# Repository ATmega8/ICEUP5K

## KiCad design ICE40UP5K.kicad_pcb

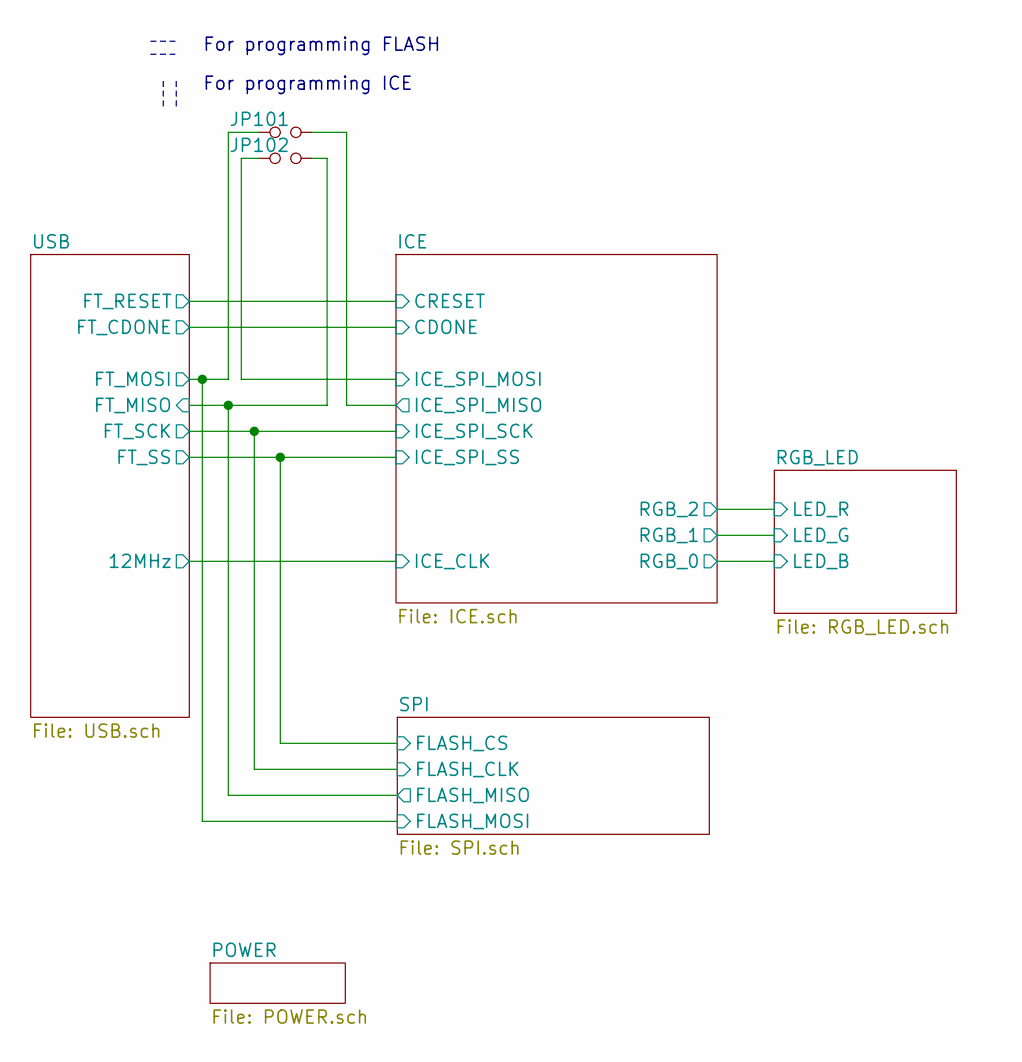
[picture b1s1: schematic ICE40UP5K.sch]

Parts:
JP101, JP102: Jumper_NO_Small; PinHeader_1x02_P2.54mm_Vertical

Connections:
/ICE/ICE_SPI_MISO: JP101.2; also elsewhere on the board
/ICE/ICE_SPI_MOSI: JP102.1; also elsewhere on the board
/SPI/FLASH_MISO: JP102.2; also elsewhere on the board
/SPI/FLASH_MOSI: JP101.1; also elsewhere on the board

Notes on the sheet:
For programming FLASH
For programming ICE

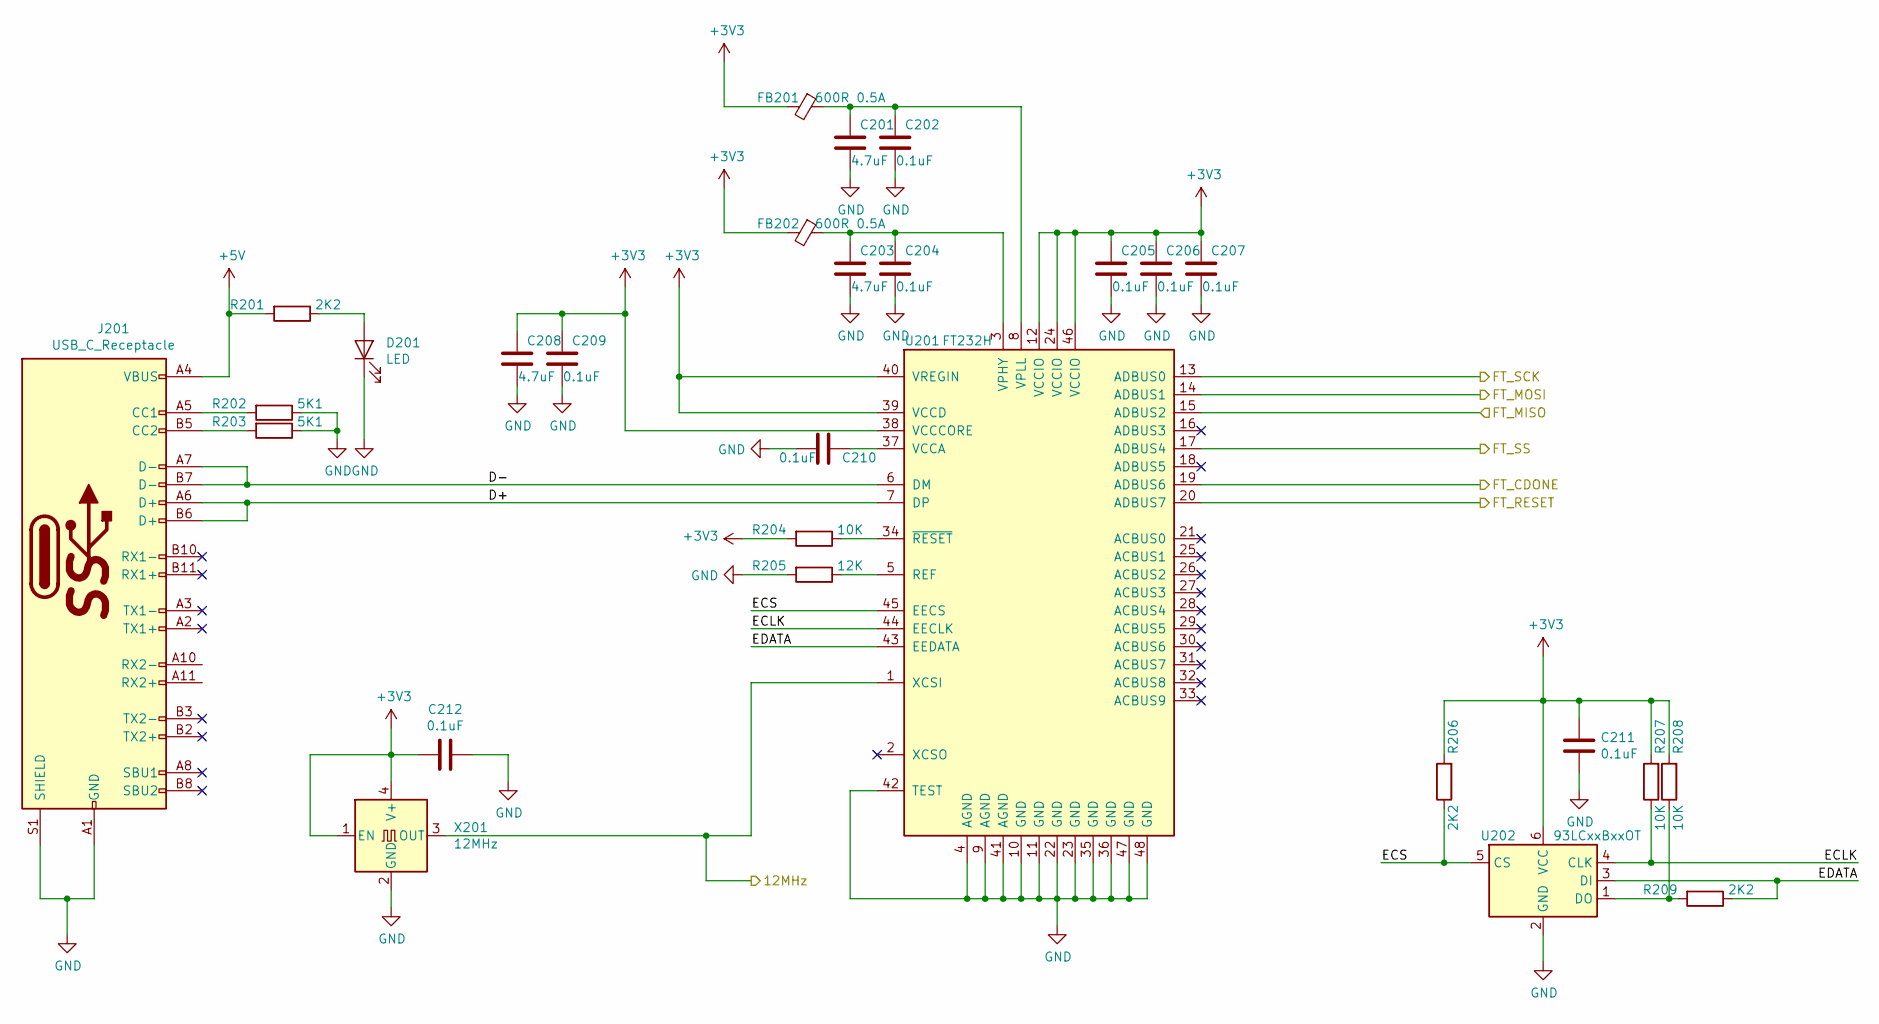
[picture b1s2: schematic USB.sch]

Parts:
C201, C203, C208: 4.7uF; C_0805_2012Metric
C202, C204, C205, C206, C207, C209, C210, C211, C212: 0.1uF; C_0603_1608Metric
D201: LED; LED_0603_1608Metric
FB201, FB202: 600R 0.5A; L_0805_2012Metric
J201: USB_C_Receptacle; USB_C_Receptacle_Palconn_UTC16-G
R201, R206, R209: 2K2; R_0603_1608Metric
R202, R203: 5K1; R_0603_1608Metric
R204, R207, R208: 10K; R_0603_1608Metric
R205: 12K; R_0603_1608Metric
U201: FT232H; LQFP-48_7x7mm_P0.5mm
U202: 93LCxxBxxOT; SOT-23-6
X201: 12MHz; Oscillator_SMD_EuroQuartz_XO32-4Pin_3.2x2.5mm_HandSoldering

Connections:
+3V3: C205.1, C206.1, C207.1, C208.1, C209.1, C211.1, C212.2, FB201.2, FB202.2, R204.2, R206.2, R207.2, R208.2, U201.12 (VCCIO), U201.24 (VCCIO), U201.38 (VCCCORE), U201.39 (VCCD), U201.40 (VREGIN), U201.46 (VCCIO), U202.6 (VCC), X201.1 (EN), X201.4 (V+); also elsewhere on the board
+5V: J201.A4 (VBUS), J201.A9 (VBUS), J201.B4 (VBUS), J201.B9 (VBUS), R201.2; also elsewhere on the board
/ICE/CDONE: U201.19 (ADBUS6); also elsewhere on the board
/ICE/CRESET: U201.20 (ADBUS7); also elsewhere on the board
/SPI/FLASH_CLK: U201.13 (ADBUS0); also elsewhere on the board
/SPI/FLASH_CS: U201.17 (ADBUS4); also elsewhere on the board
/SPI/FLASH_MISO: U201.15 (ADBUS2); also elsewhere on the board
/SPI/FLASH_MOSI: U201.14 (ADBUS1); also elsewhere on the board
/USB/12MHz: U201.1 (XCSI), X201.3 (OUT); also elsewhere on the board
/USB/D+: J201.A6 (D+), J201.B6 (D+), U201.7 (DP)
/USB/D-: J201.A7 (D-), J201.B7 (D-), U201.6 (DM)
/USB/ECLK: R207.1, U201.44 (EECLK), U202.4 (CLK)
/USB/ECS: R206.1, U201.45 (EECS), U202.5 (CS)
/USB/EDATA: R209.1, U201.43 (EEDATA), U202.3 (DI)
GND: C201.2, C202.2, C203.2, C204.2, C205.2, C206.2, C207.2, C208.2, C209.2, C210.2, C211.2, C212.1, D201.1 (K), J201.A1 (GND), J201.A12 (GND), J201.B1 (GND), J201.B12 (GND), J201.S1 (SHIELD), R202.1, R203.1, R205.2, U201.4 (AGND), U201.9 (AGND), U201.10 (GND), U201.11 (GND), U201.22 (GND), U201.23 (GND), U201.35 (GND), U201.36 (GND), U201.41 (AGND), U201.42 (TEST), U201.47 (GND), U201.48 (GND), U202.2 (GND), X201.2 (GND); also elsewhere on the board
unnamed: C201.1, C202.1, FB201.1, U201.8 (VPLL)
unnamed: C203.1, C204.1, FB202.1, U201.3 (VPHY)
unnamed: C210.1, U201.37 (VCCA)
unnamed: D201.2 (A), R201.1
unnamed: J201.A5 (CC1), R202.2
unnamed: J201.B5 (CC2), R203.2
unnamed: R204.1, U201.34 (~RESET)
unnamed: R205.1, U201.5 (REF)
unnamed: R208.1, R209.2, U202.1 (DO)

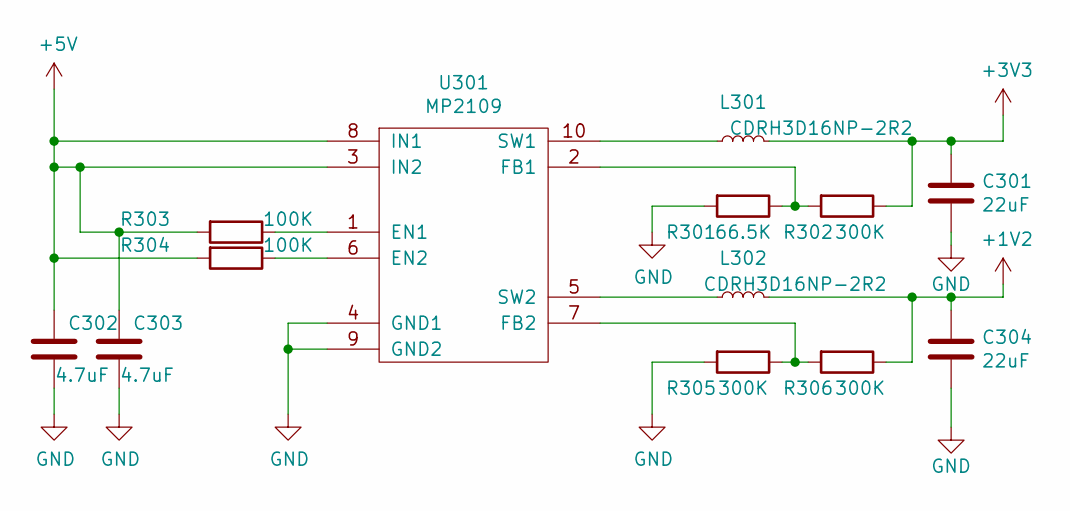
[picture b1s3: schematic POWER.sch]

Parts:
C301, C304: 22uF; C_0805_2012Metric
C302, C303: 4.7uF; C_0805_2012Metric
L301, L302: CDRH3D16NP-2R2; L_Wuerth_HCI-5040
R301: 66.5K; R_0603_1608Metric
R302, R305, R306: 300K; R_0603_1608Metric
R303, R304: 100K; R_0603_1608Metric
U301: MP2109; DFN-10-1EP_3x3mm_P0.5mm_EP1.65x2.38mm_ThermalVias

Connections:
+1V2: C304.1, L302.2, R306.1; also elsewhere on the board
+3V3: C301.1, L301.2, R302.1; also elsewhere on the board
+5V: C302.1, C303.1, R303.2, R304.2, U301.3 (IN2), U301.8 (IN1); also elsewhere on the board
GND: C301.2, C302.2, C303.2, C304.2, R301.2, R305.2, U301.4 (GND1), U301.9 (GND2); also elsewhere on the board
unnamed: L301.1, U301.10 (SW1)
unnamed: L302.1, U301.5 (SW2)
unnamed: R301.1, R302.2, U301.2 (FB1)
unnamed: R303.1, U301.1 (EN1)
unnamed: R304.1, U301.6 (EN2)
unnamed: R305.1, R306.2, U301.7 (FB2)

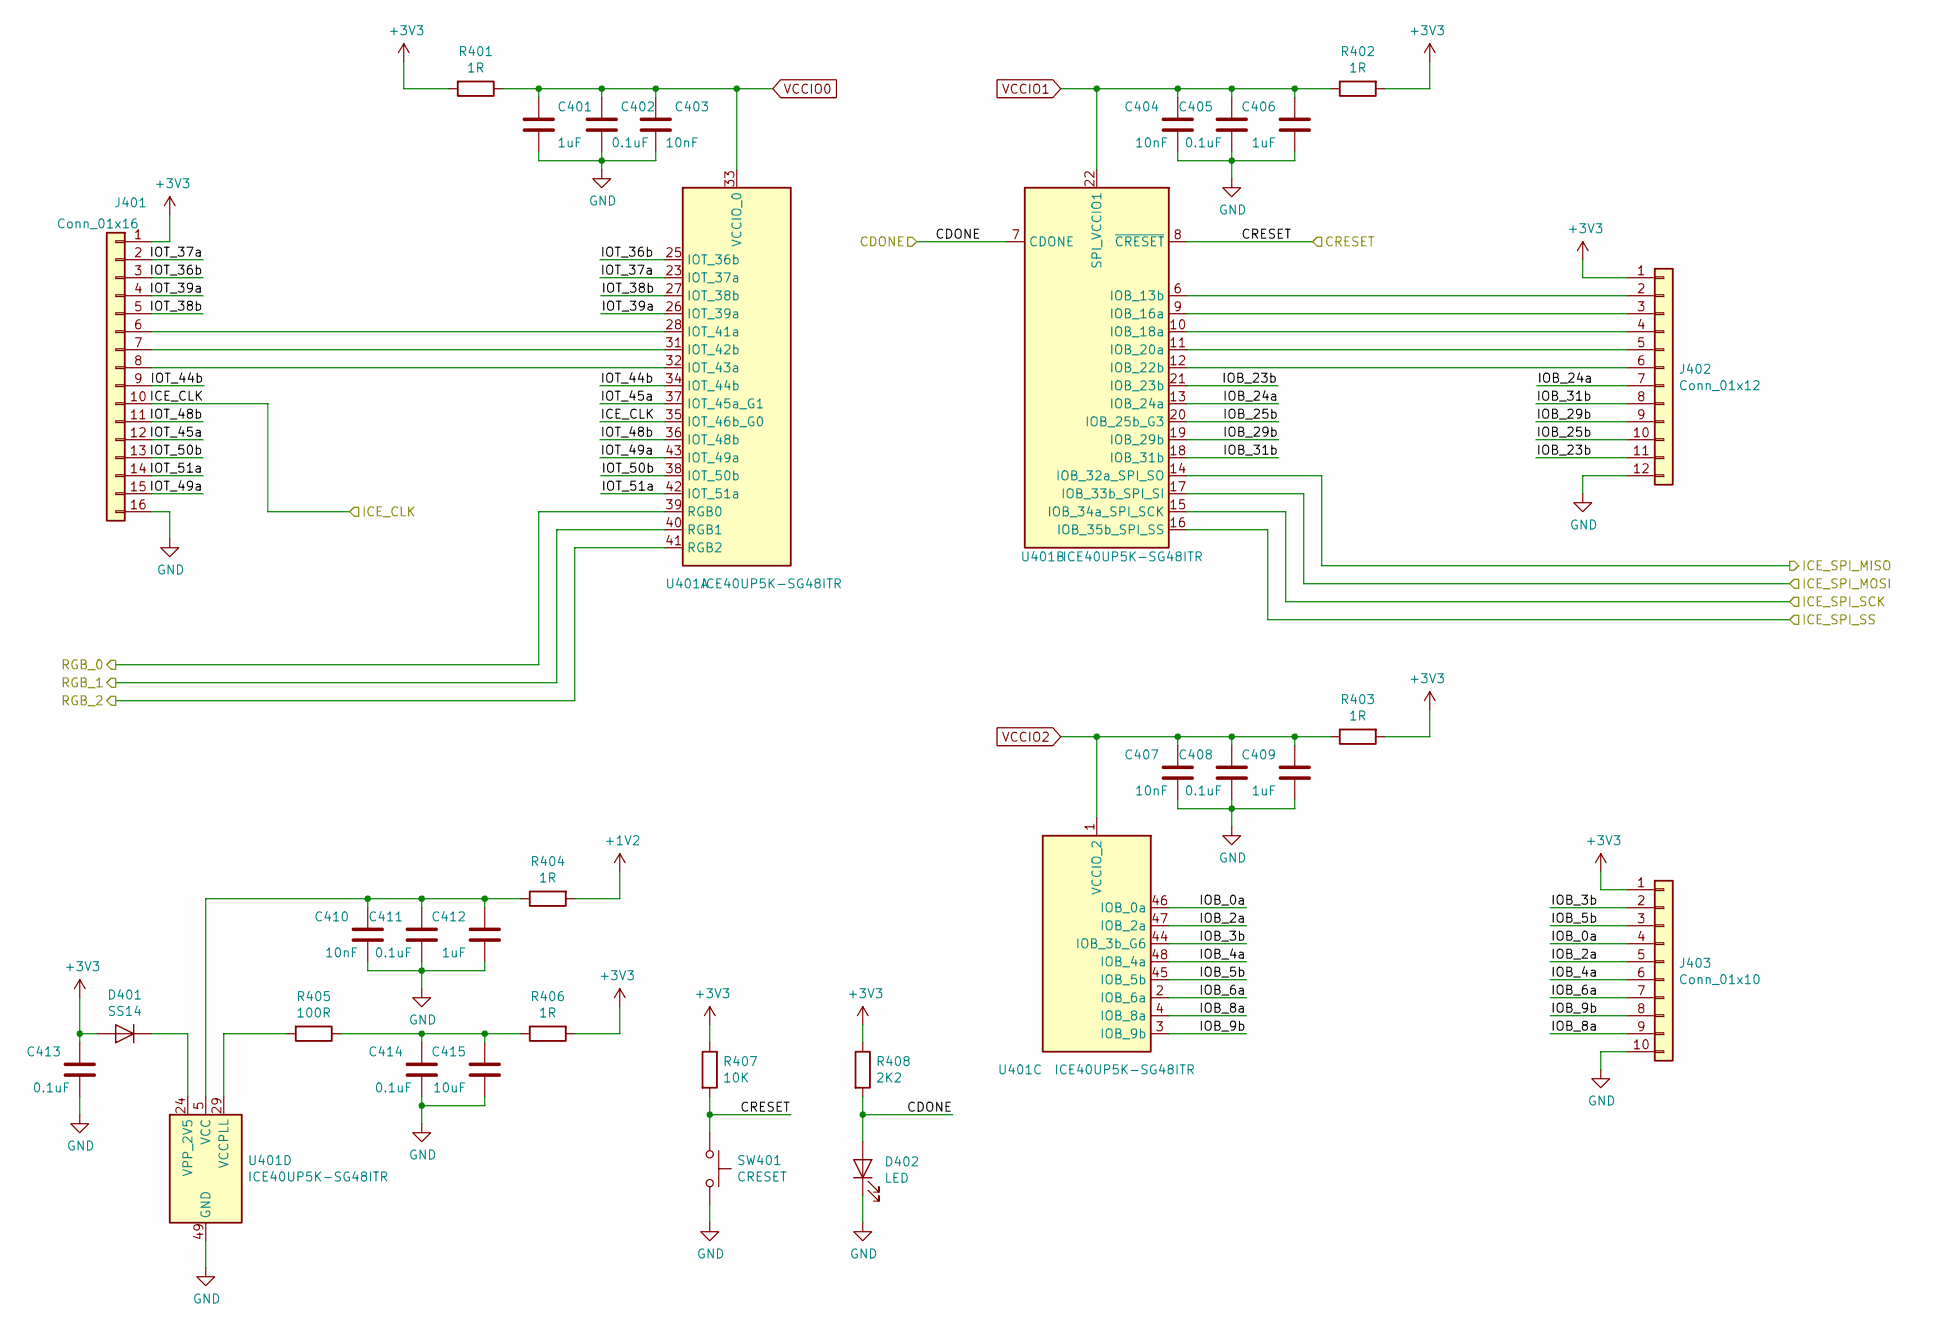
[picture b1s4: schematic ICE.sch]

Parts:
C401, C406, C409, C412: 1uF; C_0603_1608Metric
C402, C405, C408, C411, C413, C414: 0.1uF; C_0603_1608Metric
C403, C404, C407, C410: 10nF; C_0603_1608Metric
C415: 10uF; C_0805_2012Metric
D401: SS14; D_SOD-323_HandSoldering
D402: LED; LED_0603_1608Metric
J401: Conn_01x16; PinSocket_1x16_P2.54mm_Vertical
J402: Conn_01x12; PinSocket_1x12_P2.54mm_Vertical
J403: Conn_01x10; PinSocket_1x10_P2.54mm_Vertical
R401, R402, R403, R404, R406: 1R; R_0603_1608Metric
R405: 100R; R_0603_1608Metric
R407: 10K; R_0603_1608Metric
R408: 2K2; R_0603_1608Metric
SW401: CRESET; SW_SPST_TL3342
U401: ICE40UP5K-SG48ITR; QFN-48-1EP_7x7mm_P0.5mm_EP5.6x5.6mm

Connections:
+1V2: R404.2; also elsewhere on the board
+3V3: C413.1, D401.2 (A), J401.1, J402.1, J403.1, R401.2, R402.2, R403.2, R406.2, R407.1, R408.1; also elsewhere on the board
/ICE/CDONE: D402.2 (A), R408.2, U401.7 (CDONE); also elsewhere on the board
/ICE/CRESET: R407.2, SW401.1, U401.8 (~CRESET); also elsewhere on the board
/ICE/ICE_SPI_MISO: U401.14 (IOB_32a_SPI_SO); also elsewhere on the board
/ICE/ICE_SPI_MOSI: U401.17 (IOB_33b_SPI_SI); also elsewhere on the board
/ICE/IOB_0a: J403.4, U401.46 (IOB_0a)
/ICE/IOB_2a: J403.5, U401.47 (IOB_2a)
/ICE/IOB_3b: J403.2, U401.44 (IOB_3b_G6)
/ICE/IOB_4a: J403.6, U401.48 (IOB_4a)
/ICE/IOB_5b: J403.3, U401.45 (IOB_5b)
/ICE/IOB_6a: J403.7, U401.2 (IOB_6a)
/ICE/IOB_8a: J403.9, U401.4 (IOB_8a)
/ICE/IOB_9b: J403.8, U401.3 (IOB_9b)
/ICE/IOB_23b: J402.11, U401.21 (IOB_23b)
/ICE/IOB_24a: J402.7, U401.13 (IOB_24a)
/ICE/IOB_25b: J402.10, U401.20 (IOB_25b_G3)
/ICE/IOB_29b: J402.9, U401.19 (IOB_29b)
/ICE/IOB_31b: J402.8, U401.18 (IOB_31b)
/ICE/IOT_36b: J401.3, U401.25 (IOT_36b)
/ICE/IOT_37a: J401.2, U401.23 (IOT_37a)
/ICE/IOT_38b: J401.5, U401.27 (IOT_38b)
/ICE/IOT_39a: J401.4, U401.26 (IOT_39a)
/ICE/IOT_44b: J401.9, U401.34 (IOT_44b)
/ICE/IOT_45a: J401.12, U401.37 (IOT_45a_G1)
/ICE/IOT_48b: J401.11, U401.36 (IOT_48b)
/ICE/IOT_49a: J401.15, U401.43 (IOT_49a)
/ICE/IOT_50b: J401.13, U401.38 (IOT_50b)
/ICE/IOT_51a: J401.14, U401.42 (IOT_51a)
/RGB_LED/LED_B: U401.39 (RGB0); also elsewhere on the board
/RGB_LED/LED_G: U401.40 (RGB1); also elsewhere on the board
/RGB_LED/LED_R: U401.41 (RGB2); also elsewhere on the board
/SPI/FLASH_CLK: U401.15 (IOB_34a_SPI_SCK); also elsewhere on the board
/SPI/FLASH_CS: U401.16 (IOB_35b_SPI_SS); also elsewhere on the board
/USB/12MHz: J401.10, U401.35 (IOT_46b_G0); also elsewhere on the board
GND: C401.2, C402.2, C403.2, C404.2, C405.2, C406.2, C407.2, C408.2, C409.2, C410.2, C411.2, C412.2, C413.2, C414.2, C415.2, D402.1 (K), J401.16, J402.12, J403.10, SW401.2, U401.49 (GND); also elsewhere on the board
unnamed: C410.1, C411.1, C412.1, R404.1, U401.5 (VCC), U401.30 (VCC)
unnamed: C414.1, C415.1, R405.1, R406.1
unnamed: D401.1 (K), U401.24 (VPP_2V5)
unnamed: J401.6, U401.28 (IOT_41a)
unnamed: J401.7, U401.31 (IOT_42b)
unnamed: J401.8, U401.32 (IOT_43a)
unnamed: J402.2, U401.6 (IOB_13b)
unnamed: J402.3, U401.9 (IOB_16a)
unnamed: J402.4, U401.10 (IOB_18a)
unnamed: J402.5, U401.11 (IOB_20a)
unnamed: J402.6, U401.12 (IOB_22b)
unnamed: R405.2, U401.29 (VCCPLL)
VCCIO0: C401.1, C402.1, C403.1, R401.1, U401.33 (VCCIO_0)
VCCIO1: C404.1, C405.1, C406.1, R402.1, U401.22 (SPI_VCCIO1)
VCCIO2: C407.1, C408.1, C409.1, R403.1, U401.1 (VCCIO_2)

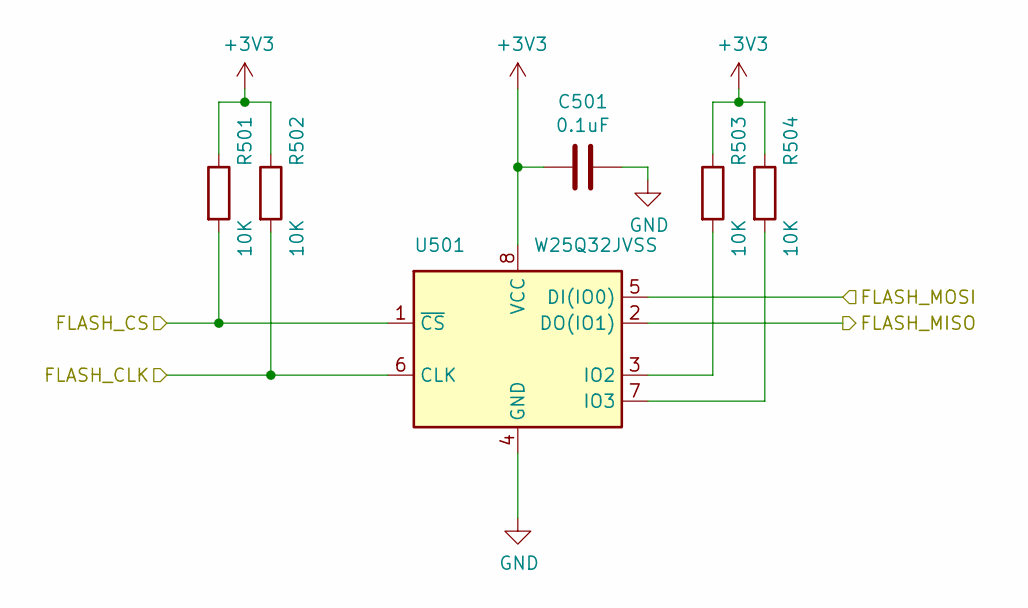
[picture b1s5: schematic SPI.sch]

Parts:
C501: 0.1uF; C_0603_1608Metric
R501, R502, R503, R504: 10K; R_0603_1608Metric
U501: W25Q32JVSS; SOIC-8_5.23x5.23mm_P1.27mm

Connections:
+3V3: C501.1, R501.1, R502.1, R503.1, R504.1, U501.8 (VCC); also elsewhere on the board
/SPI/FLASH_CLK: R502.2, U501.6 (CLK); also elsewhere on the board
/SPI/FLASH_CS: R501.2, U501.1 (~CS); also elsewhere on the board
/SPI/FLASH_MISO: U501.2 (DO(IO1)); also elsewhere on the board
/SPI/FLASH_MOSI: U501.5 (DI(IO0)); also elsewhere on the board
GND: C501.2, U501.4 (GND); also elsewhere on the board
unnamed: R503.2, U501.3 (IO2)
unnamed: R504.2, U501.7 (IO3)

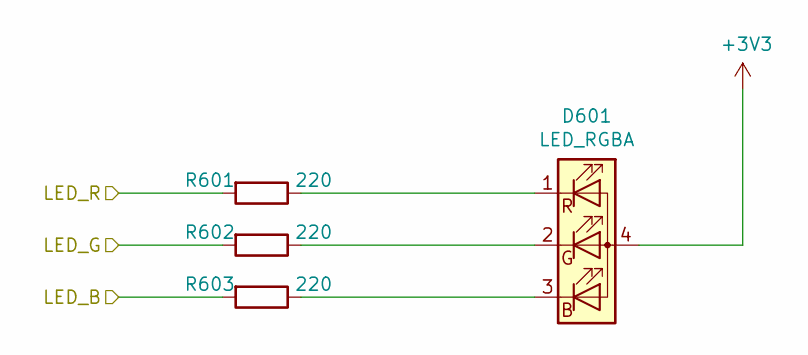
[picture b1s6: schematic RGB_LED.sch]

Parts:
D601: LED_RGBA; LED_Cree-PLCC4_2x2mm_CW
R601, R602, R603: 220; R_0603_1608Metric

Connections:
+3V3: D601.4 (A); also elsewhere on the board
/RGB_LED/LED_B: R603.2; also elsewhere on the board
/RGB_LED/LED_G: R602.2; also elsewhere on the board
/RGB_LED/LED_R: R601.2; also elsewhere on the board
unnamed: D601.1 (RK), R601.1
unnamed: D601.2 (GK), R602.1
unnamed: D601.3 (BK), R603.1

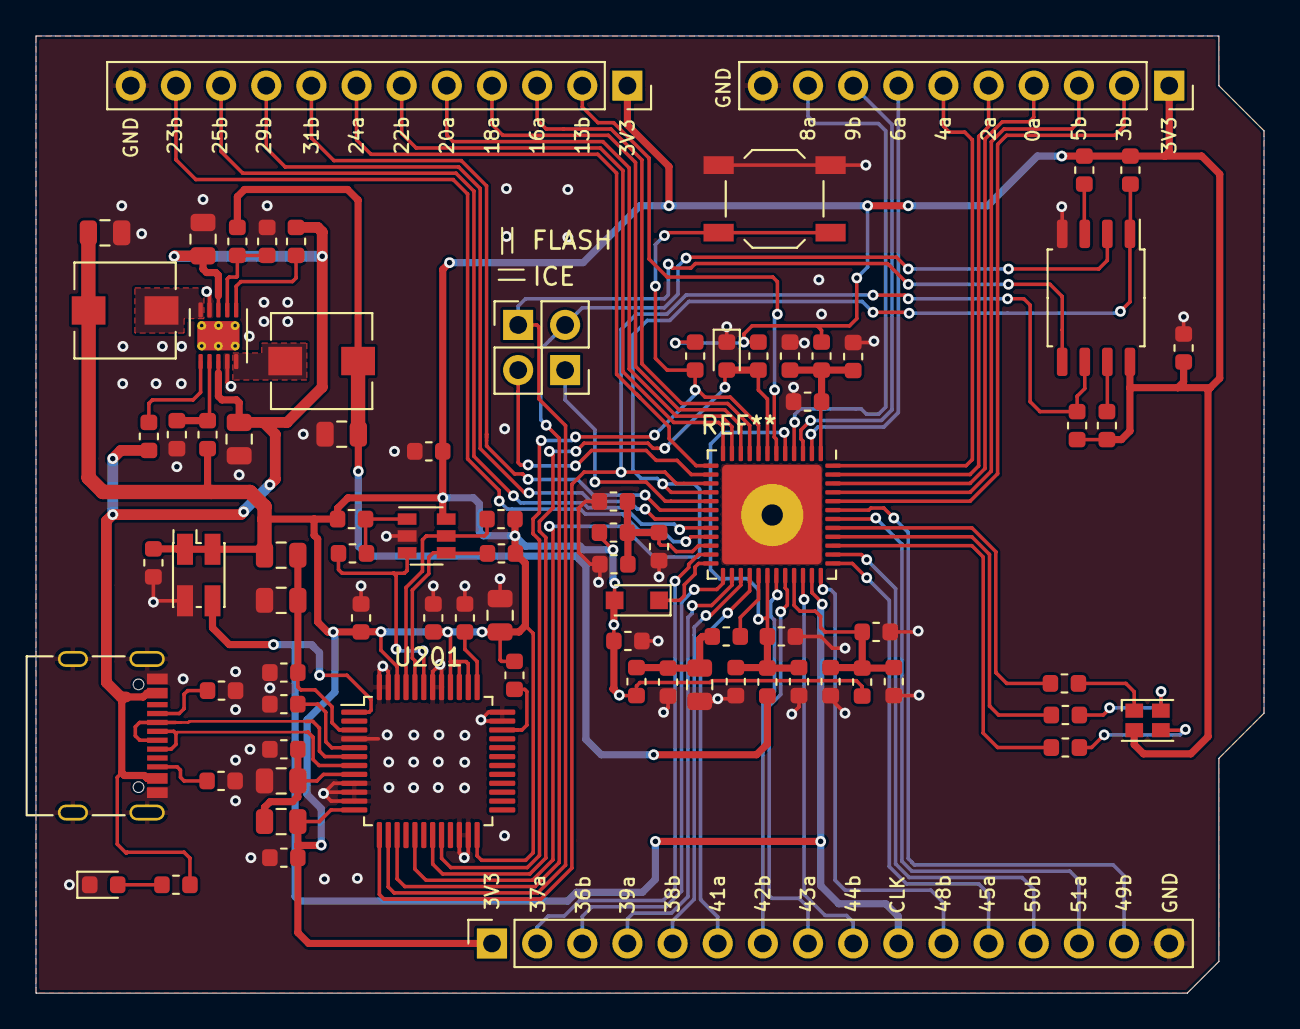
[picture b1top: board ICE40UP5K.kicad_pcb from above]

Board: 2 copper layers, 69.1 x 53.8 mm, 82 parts (0 on the bottom side), 79 nets.

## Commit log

2019-12-08 add readme
